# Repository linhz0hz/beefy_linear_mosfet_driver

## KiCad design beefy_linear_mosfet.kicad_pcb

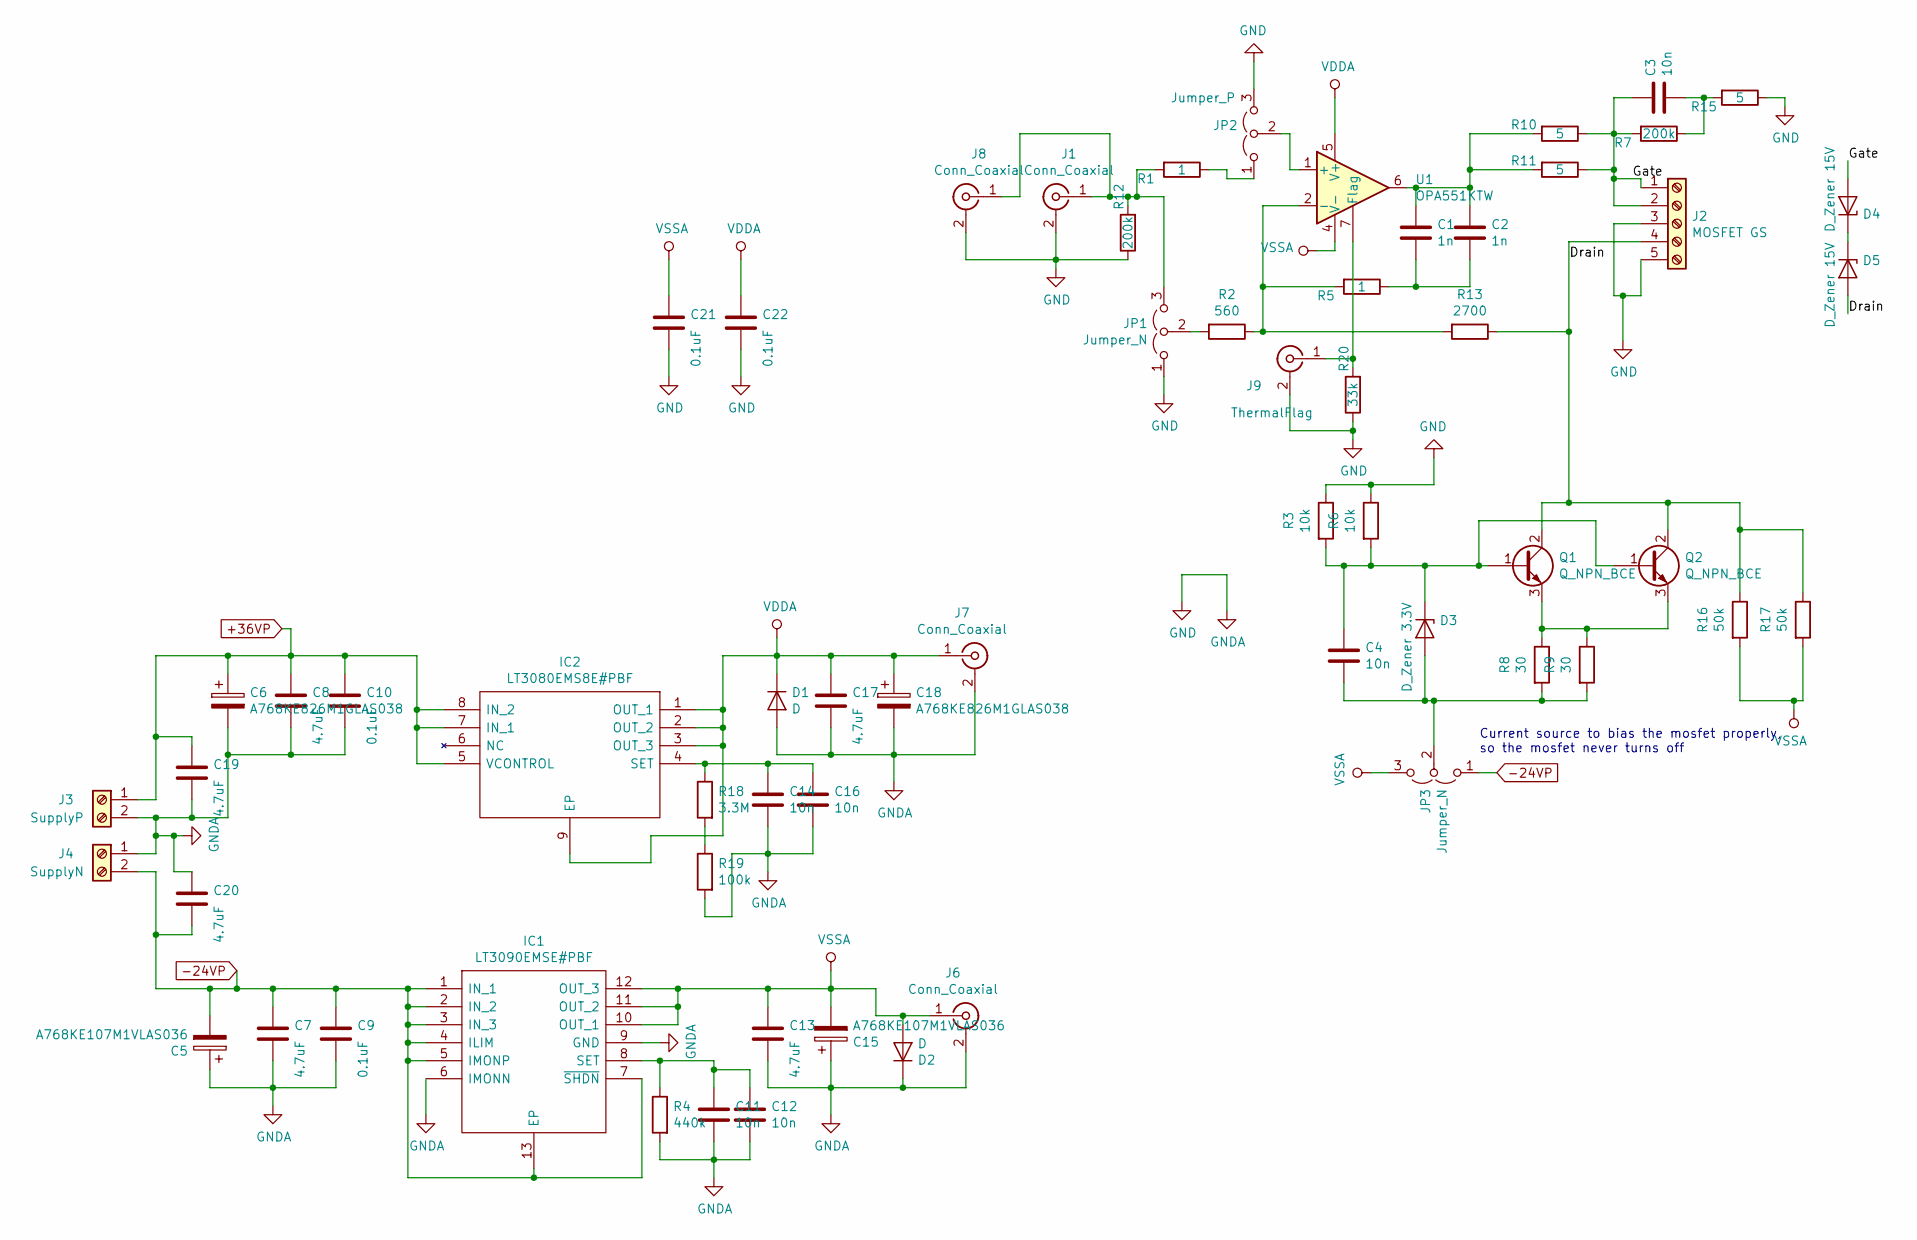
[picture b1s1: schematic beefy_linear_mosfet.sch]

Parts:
C1: 1n; C_Disc_D3.8mm_W2.6mm_P2.50mm
C2: 1n; C_1206_0805_dual
C3, C4, C11, C12, C14, C16: 10n; C_1206_0805_dual
C5, C15: A768KE107M1VLAS036; CP_Elec_8x6.7
C6, C18: A768KE826M1GLAS038; CP_Elec_8x6.7
C7, C8, C13, C17, C19, C20: 4.7uF; C_1206_3216Metric_Pad1.42x1.75mm_HandSolder
C9, C10, C21, C22: 0.1uF; C_0805_2012Metric_Pad1.15x1.40mm_HandSolder
D1, D2: D; D_DO-35_SOD27_P7.62mm_Horizontal
D3: D_Zener 3.3V; D_DO-35_SOD27_P7.62mm_Horizontal
D4, D5: D_Zener 15V; D_DO-35_SOD27_P7.62mm_Horizontal
IC1: LT3090EMSE#PBF; SOP65P490X110-13N; Mouser Part Number 584-LT3090EMSE#PBF
IC2: LT3080EMS8E#PBF; SOP65P490X110-9N; Mouser Part Number 584-LT3080EMS8E#PBF
J1: Conn_Coaxial; SMA_Amphenol_132134-10_Vertical
J2: MOSFET GS; TerminalBlock_bornier-5_P5.08mm
J3: SupplyP; TerminalBlock_bornier-2_P5.08mm
J4: SupplyN; TerminalBlock_bornier-2_P5.08mm
J6, J7: Conn_Coaxial; Coaxial_IPX_TE_23370191-1-2
J8: Conn_Coaxial; SMA_Amphenol_132134-11_Vertical
J9: ThermalFlag; Coaxial_IPX_TE_23370191-1-2
JP1, JP3: Jumper_N; PinHeader_1x03_P2.54mm_Vertical
JP2: Jumper_P; PinHeader_1x03_P2.54mm_Vertical
Q1, Q2: Q_NPN_BCE; TO-252-2
R1, R5: 1; R_0805_2012Metric_Pad1.15x1.40mm_HandSolder
R2: 560; R_Axial_DIN0309_L9.0mm_D3.2mm_P12.70mm_Horizontal
R3, R6: 10k; R_Axial_DIN0309_L9.0mm_D3.2mm_P12.70mm_Horizontal
R4: 440k; R_0805_2012Metric_Pad1.15x1.40mm_HandSolder
R7, R12: 200k; R_1206_0805_dual
R8, R9: 30; R_Axial_DIN0309_L9.0mm_D3.2mm_P12.70mm_Horizontal
R10, R11: 5; R_Axial_DIN0309_L9.0mm_D3.2mm_P12.70mm_Horizontal
R13: 2700; R_Axial_DIN0617_L17.0mm_D6.0mm_P25.40mm_Horizontal
R15: 5; R_1206_3216Metric_Pad1.42x1.75mm_HandSolder
R16, R17: 50k; R_Axial_DIN0309_L9.0mm_D3.2mm_P12.70mm_Horizontal
R18: 3.3M; R_0805_2012Metric_Pad1.15x1.40mm_HandSolder
R19: 100k; R_0805_2012Metric_Pad1.15x1.40mm_HandSolder
R20: 33k; R_0805_2012Metric_Pad1.15x1.40mm_HandSolder
U1: OPA551KTW; TO-263-7_TabPin4

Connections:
+36VP: C6.1, C8.1, C10.1, C19.1, IC2.5 (VCONTROL), IC2.7 (IN_1), IC2.8 (IN_2), J3.1
-24VP: C5.2, C7.1, C9.1, C20.2, IC1.1 (IN_1), IC1.2 (IN_2), IC1.3 (IN_3), IC1.4 (ILIM), IC1.5 (IMONP), IC1.7 (~SHDN), IC1.13 (EP), J4.2, JP3.1 (A)
/Drain: D5.2 (A), J2.4, Q1.2 (C), Q2.2 (C), R13.1, R16.1, R17.1
/Gate: C3.1, D4.2 (A), J2.1, J2.2, R7.2, R10.1, R11.1
GND: C5.1, C6.2, C7.2, C8.2, C9.2, C10.2, C11.2, C12.2, C13.2, C14.2, C15.1, C16.2, C17.2, C18.2, C19.2, C20.1, C21.2, C22.2, D1.2 (A), D2.1 (K), IC1.6 (IMONN), IC1.9 (GND), J1.2 (Ext), J2.3, J2.5, J3.2, J4.1, J6.2 (Ext), J7.2 (Ext), J8.2 (Ext), J9.2 (Ext), JP1.1 (A), JP2.3 (B), R3.1, R4.2, R6.1, R12.1, R15.1, R19.2, R20.1
unnamed: C1.1, C2.1, R10.2, R11.2, U1.6
unnamed: C1.2, C2.2, R5.1
unnamed: C3.2, R7.1, R15.2
unnamed: C4.1, D3.1 (K), Q1.1 (B), Q2.1 (B), R3.2, R6.2
unnamed: C4.2, D3.2 (A), JP3.2 (C), R8.2, R9.2
unnamed: C11.1, C12.1, IC1.8 (SET), R4.1
unnamed: C14.1, C16.1, IC2.4 (SET), R18.1
unnamed: D4.1 (K), D5.1 (K)
unnamed: J1.1 (In), J8.1 (In), JP1.3 (B), R1.2, R12.2
unnamed: J9.1 (In), R20.2, U1.7 (Flag)
unnamed: JP1.2 (C), R2.2
unnamed: JP2.1 (A), R1.1
unnamed: JP2.2 (C), U1.1 (+)
unnamed: Q1.3 (E), Q2.3 (E), R8.1, R9.1
unnamed: R2.1, R5.2, R13.2, U1.2 (-)
unnamed: R18.2, R19.1
VDDA: C17.1, C18.1, C22.1, D1.1 (K), IC2.1 (OUT_1), IC2.2 (OUT_2), IC2.3 (OUT_3), IC2.9 (EP), J7.1 (In), U1.5 (V+)
VSSA: C13.1, C15.2, C21.1, D2.2 (A), IC1.10 (OUT_1), IC1.11 (OUT_2), IC1.12 (OUT_3), J6.1 (In), JP3.3 (B), R16.2, R17.2, U1.4 (V-)

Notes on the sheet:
Current source to bias the mosfet properly, so the mosfet never turns off

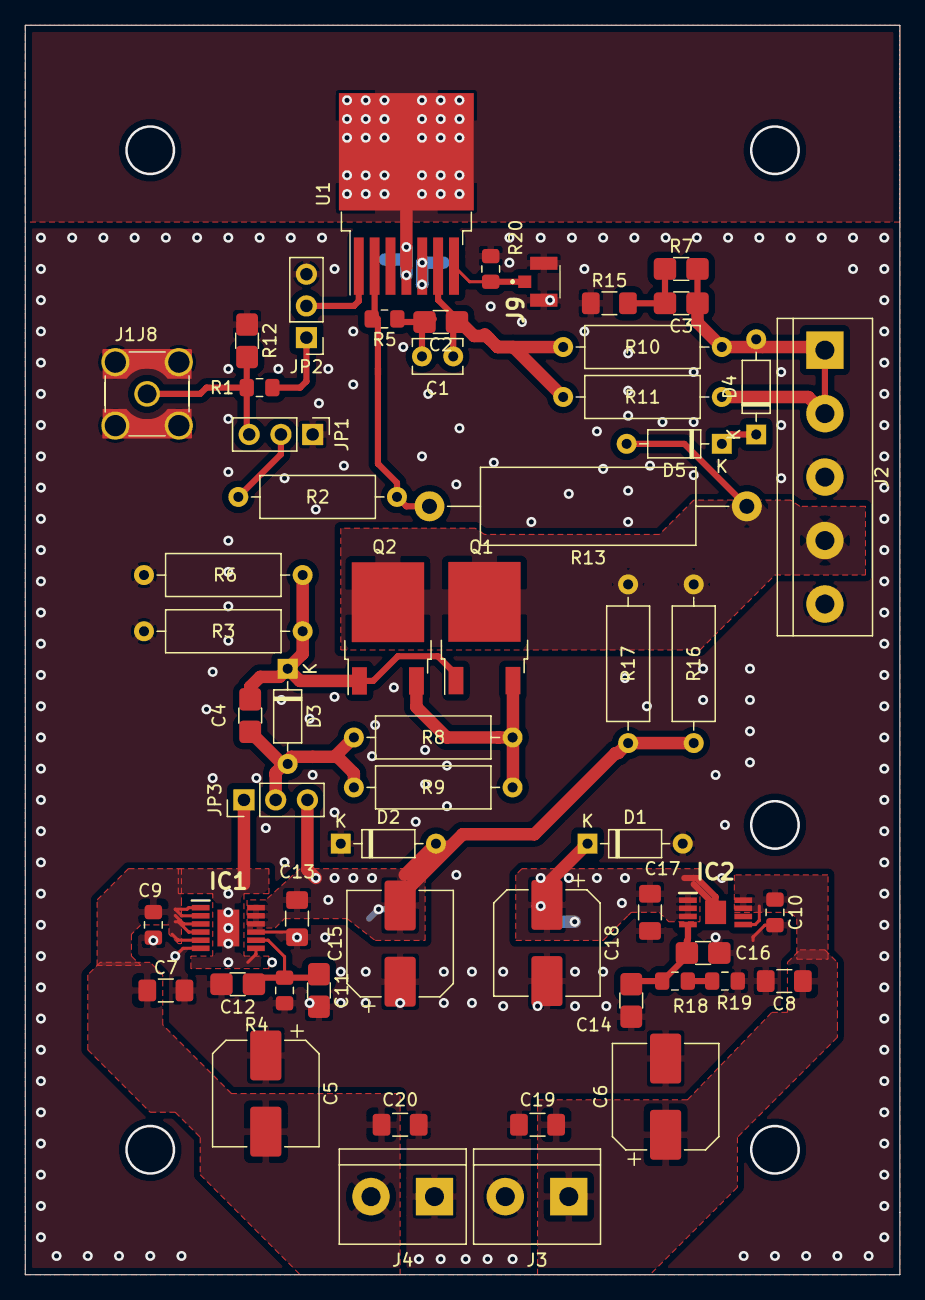
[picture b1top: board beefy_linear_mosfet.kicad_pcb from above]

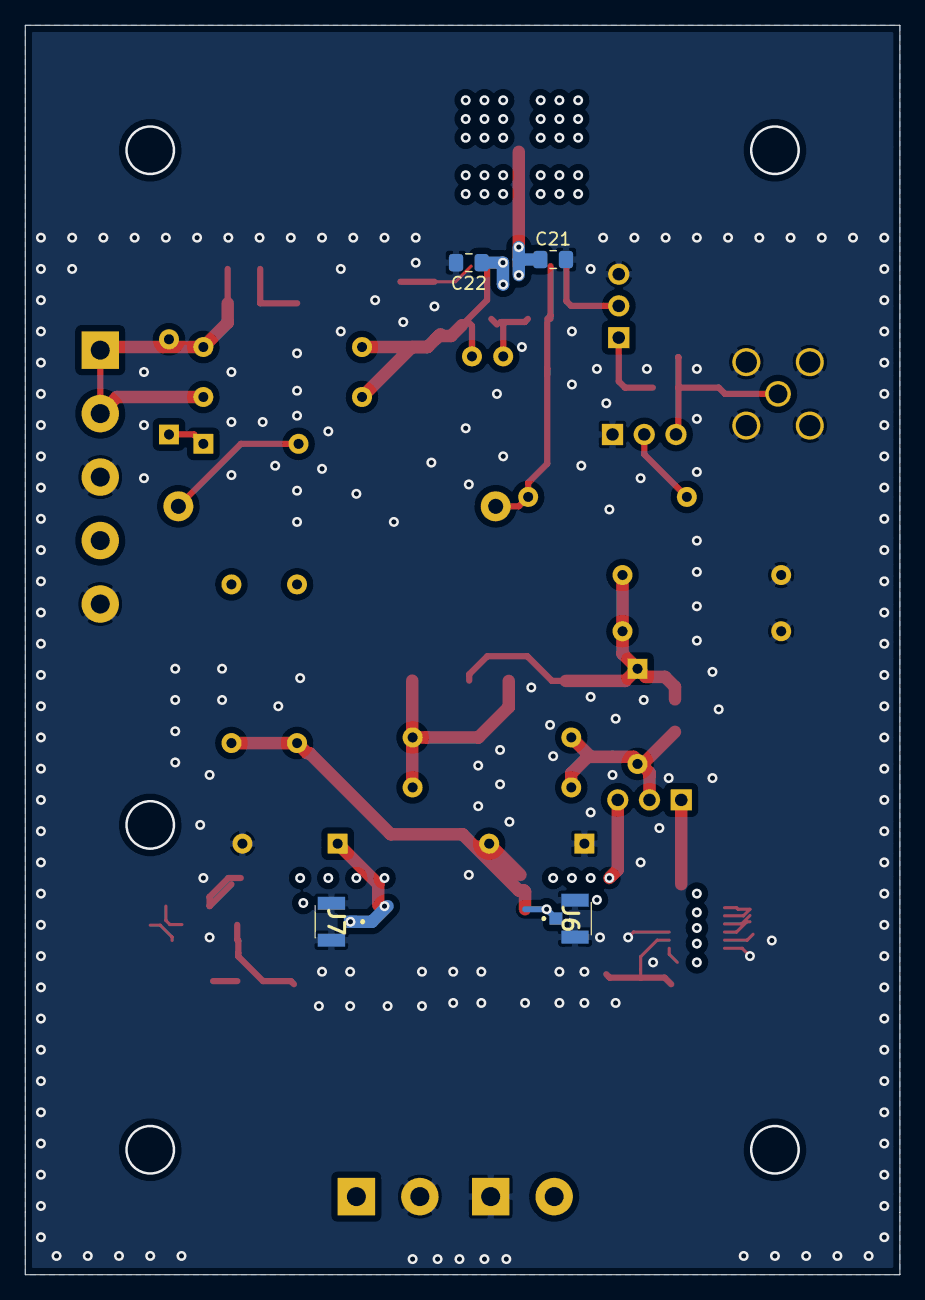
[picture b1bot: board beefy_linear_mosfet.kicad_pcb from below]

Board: 4 copper layers, 70.0 x 100.0 mm, 62 parts (4 on the bottom side), 23 nets.

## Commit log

2021-09-03 Update prototype effor so far
